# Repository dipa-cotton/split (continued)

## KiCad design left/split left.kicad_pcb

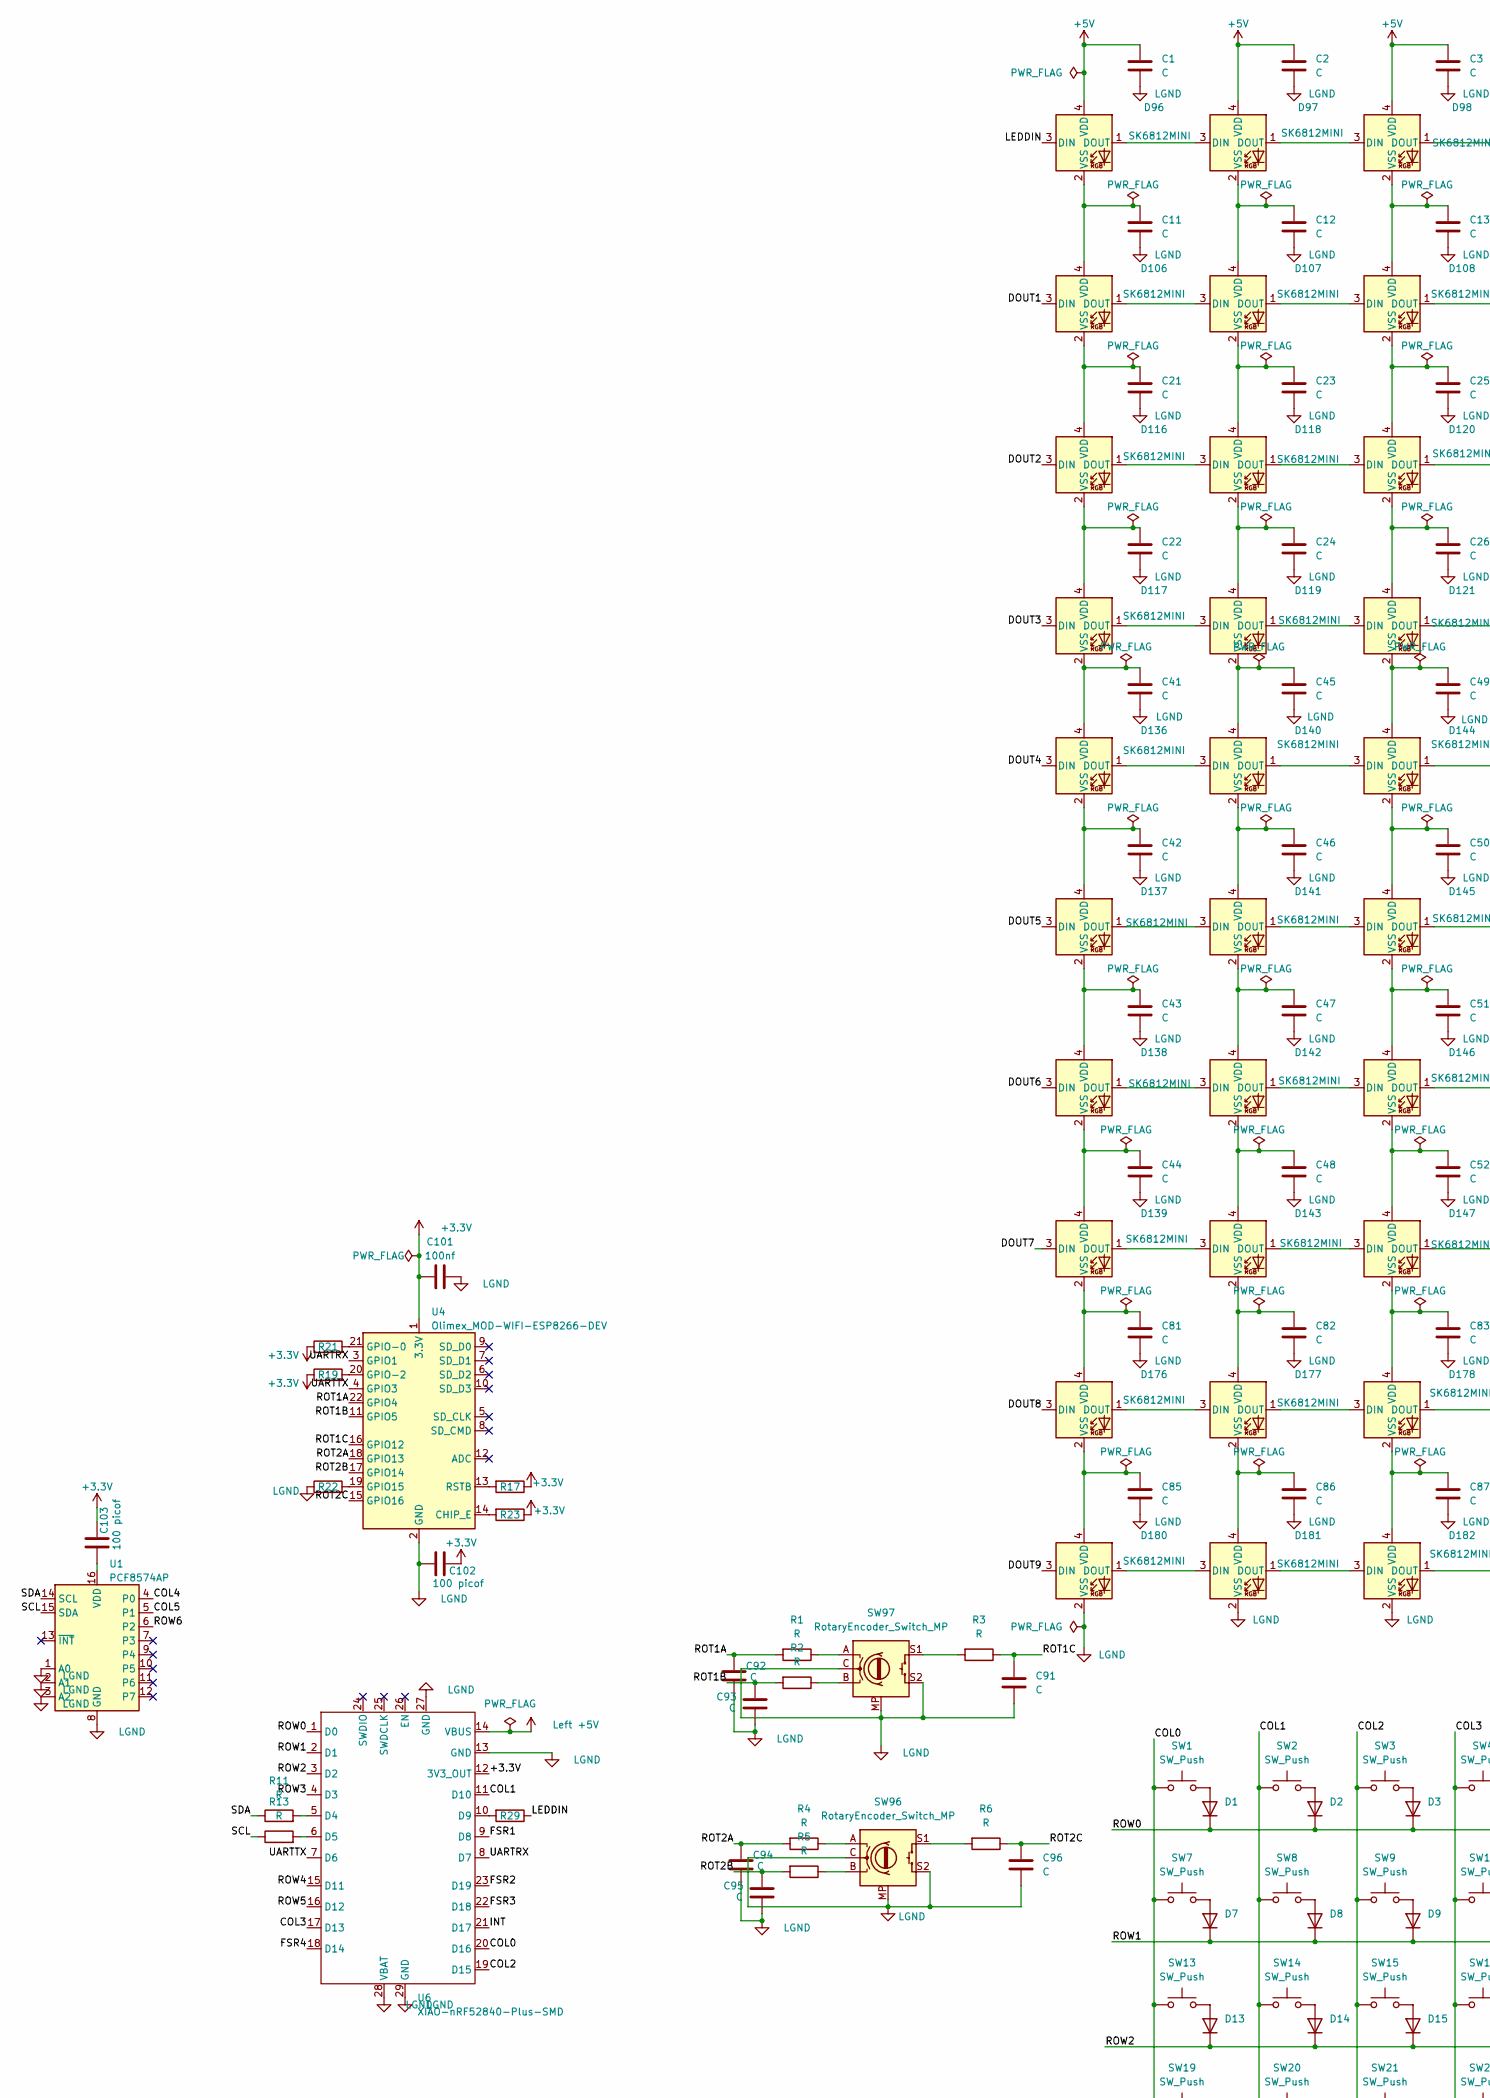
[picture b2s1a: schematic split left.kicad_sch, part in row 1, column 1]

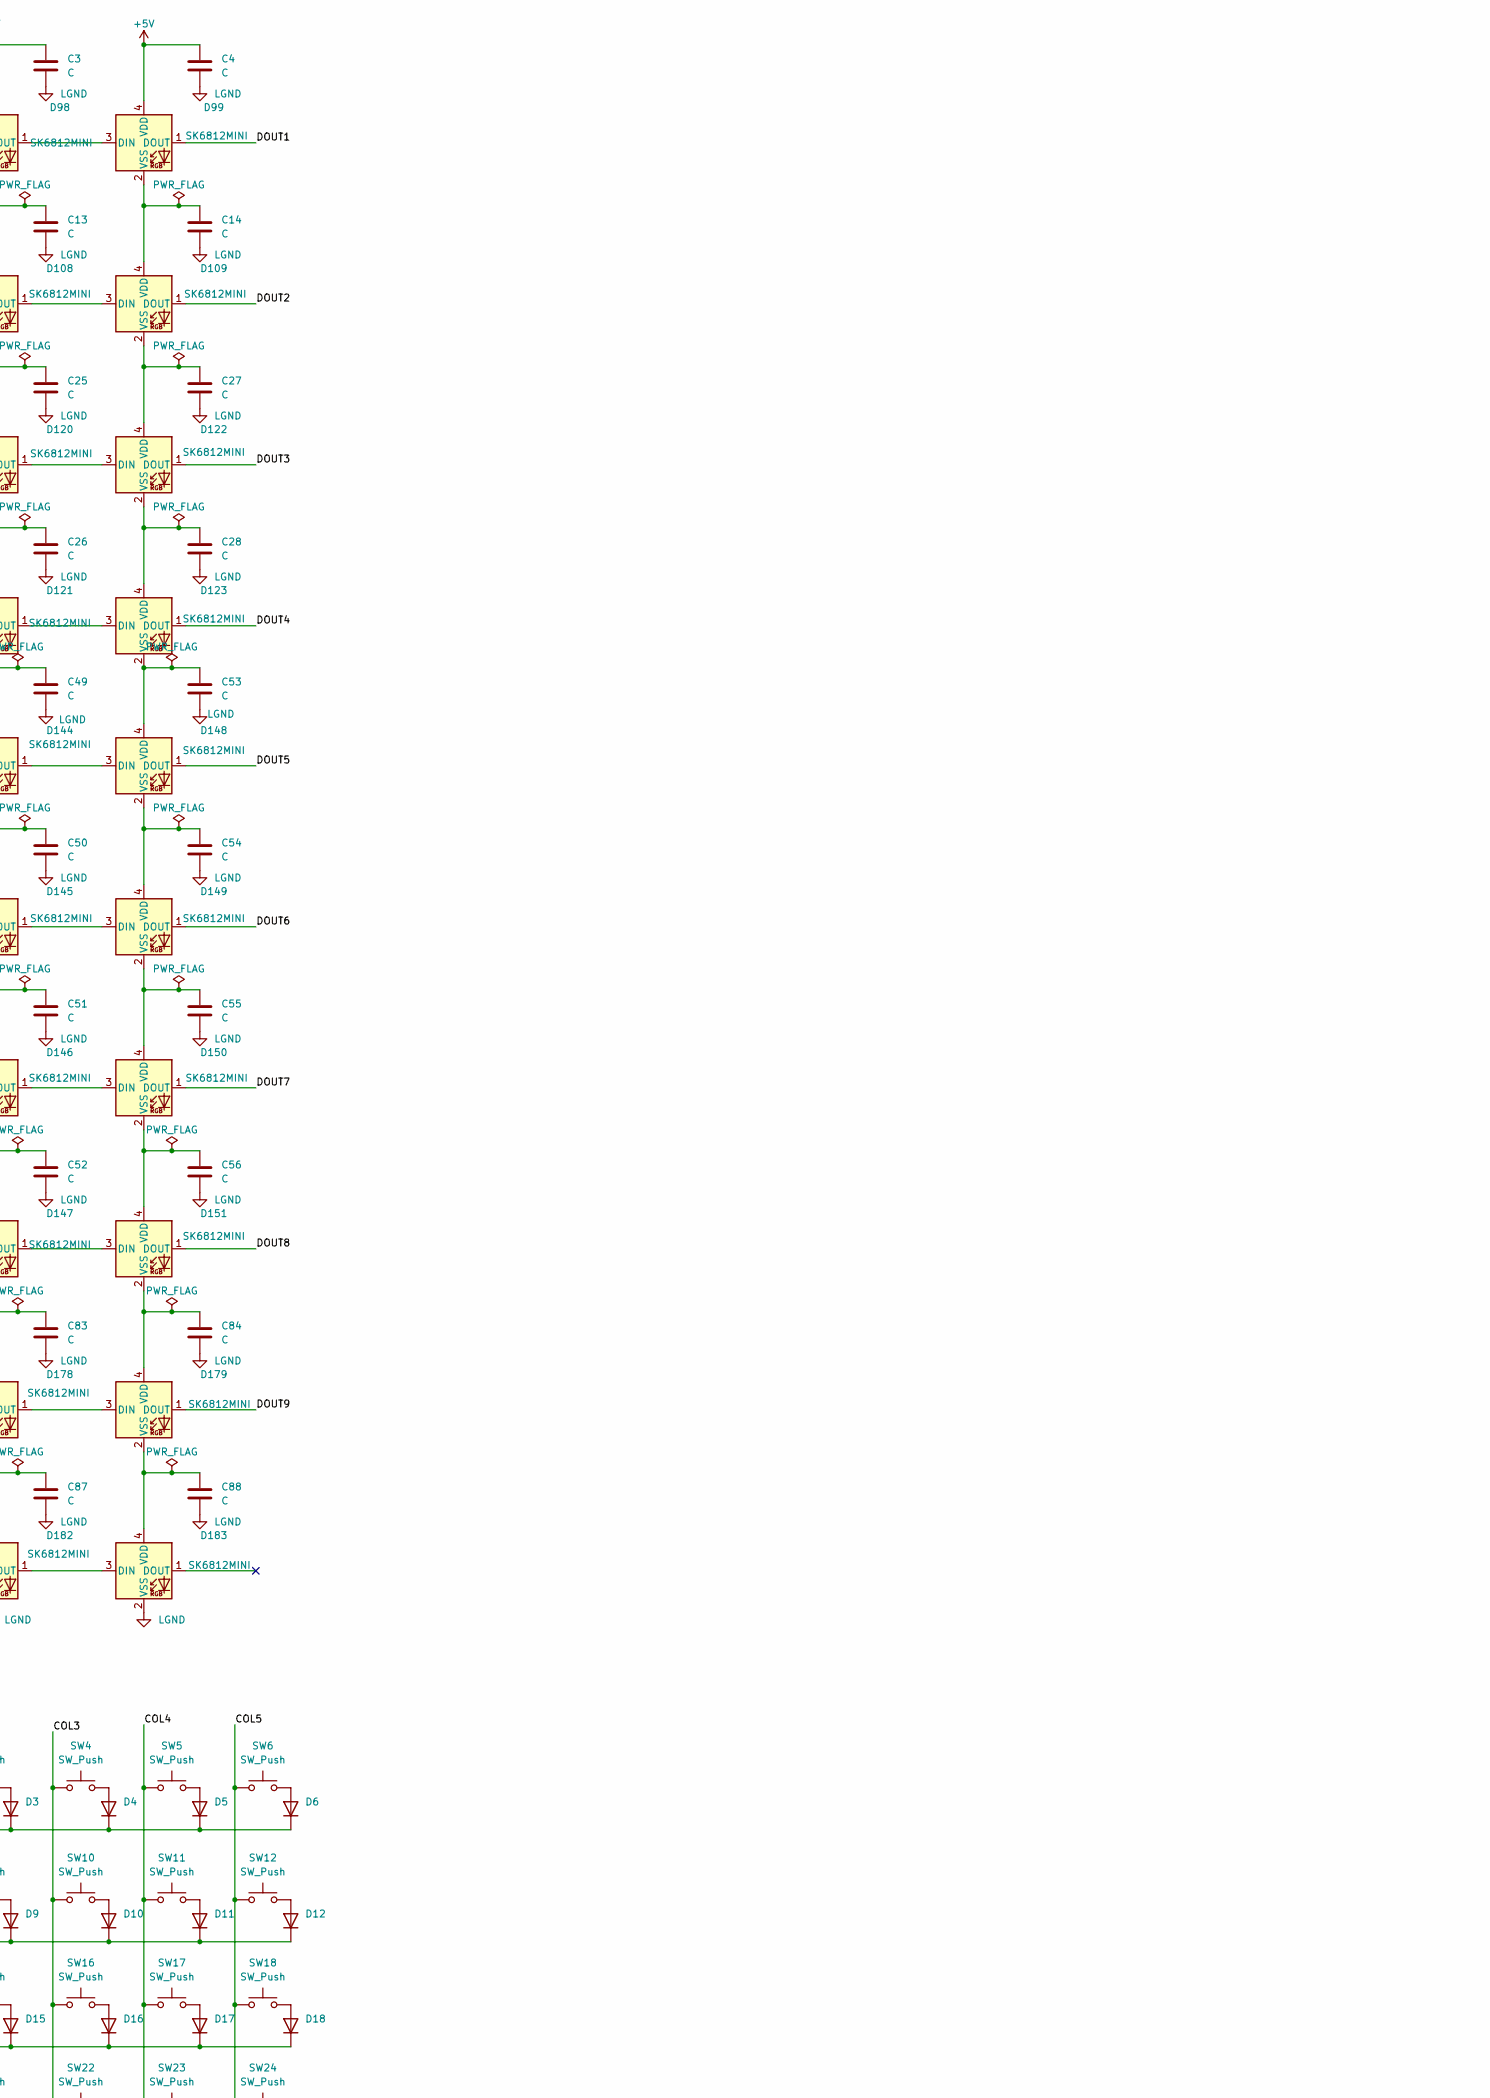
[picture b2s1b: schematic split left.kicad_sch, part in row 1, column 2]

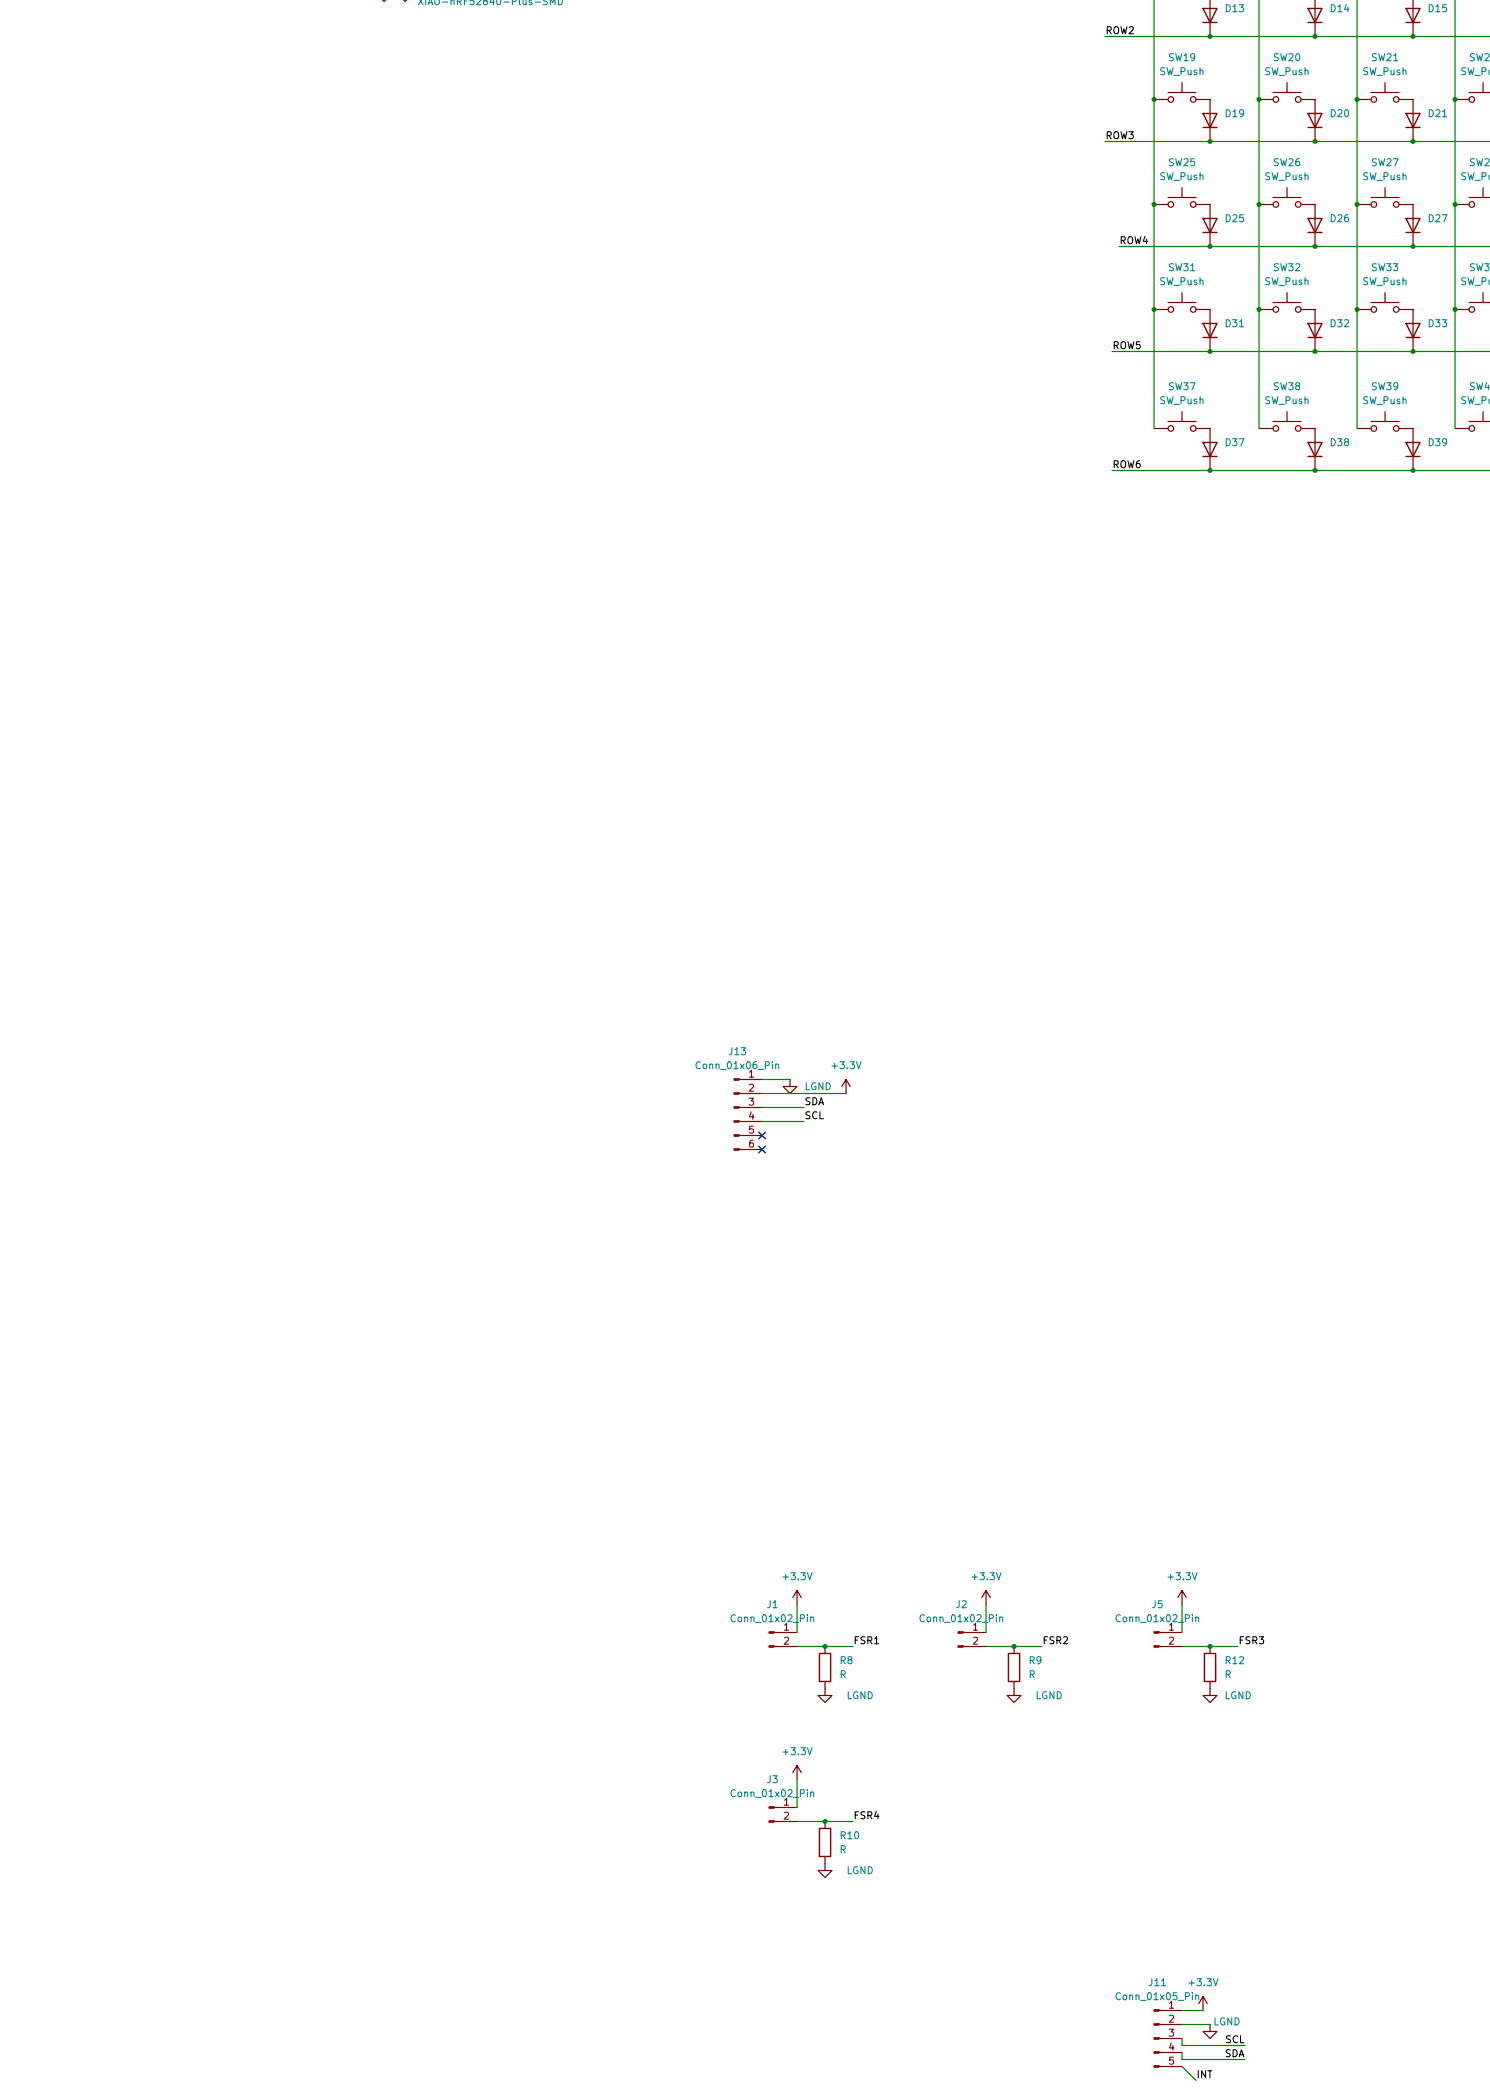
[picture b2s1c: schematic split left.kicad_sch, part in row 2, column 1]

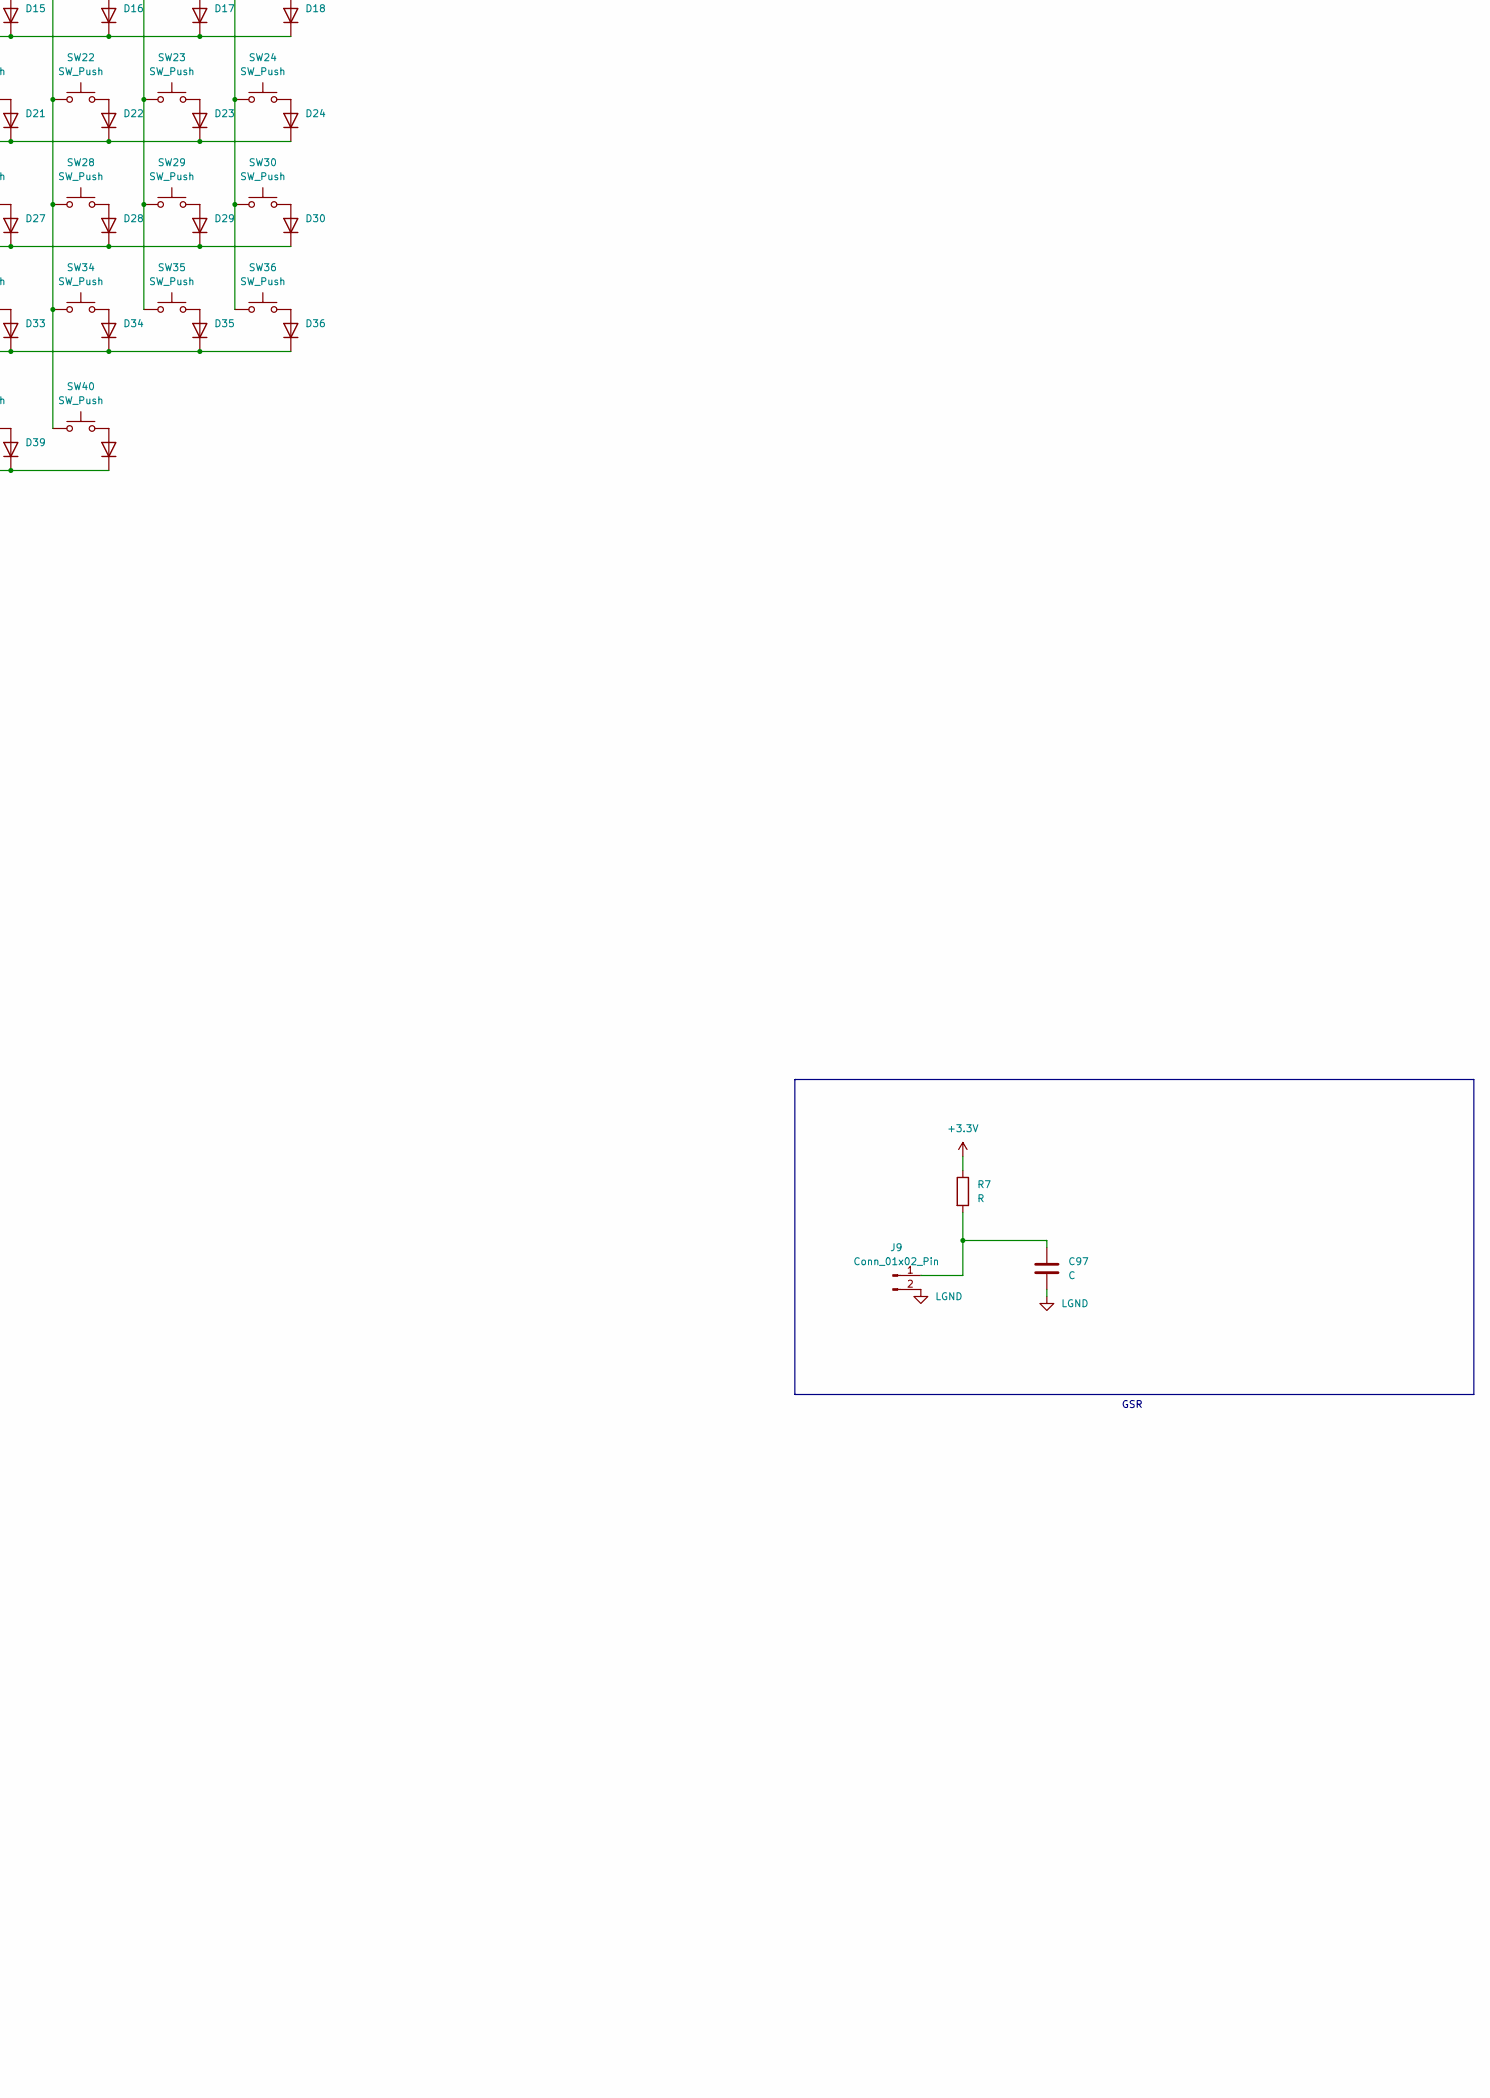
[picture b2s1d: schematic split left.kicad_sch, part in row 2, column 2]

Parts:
C1, C2, C3, C4, C11, C12, C13, C14, C21, C22, C23, C24, C25, C26, C27, C28, C41, C42, C43, C44, C45, C46, C47, C48, C49, C50, C51, C52, C53, C54, C55, C56, C81, C82, C83, C84, C85, C86, C87, C88, C91, C92, C93, C94, C95, C96, C97: C; C_0603_1608Metric
C101: 100nf; C_0603_1608Metric
C102, C103: 100 picof; C_0603_1608Metric
D1, D2, D3, D4, D5, D6, D7, D8, D9, D10, D11, D12, D13, D14, D15, D16, D17, D18, D19, D20, D21, D22, D23, D24, D25, D26, D27, D28, D29, D30, D31, D32, D33, D34, D35, D36, D37, D38, D39, D40: 1N914; C_0603_1608Metric
D96, D97, D98, D99, D106, D107, D108, D109, D116, D117, D118, D119, D120, D121, D122, D123, D136, D137, D138, D139, D140, D141, D142, D143, D144, D145, D146, D147, D148, D149, D150, D151, D176, D177, D178, D179, D180, D181, D182, D183: SK6812MINI; LED_SK6812MINI_PLCC4_3.5x3.5mm_P1.75mm
J1, J2, J3, J5, J9: Conn_01x02_Pin; TestPoint_Bridge_Pitch2.54mm_Drill1.0mm
J11: Conn_01x05_Pin; PinSocket_1x05_P2.54mm_Vertical
J13: Conn_01x06_Pin; PinHeader_1x06_P2.54mm_Vertical
R1, R2, R3, R4, R5, R6, R7, R8, R9, R10, R12, R17, R19, R21, R22, R23, R29: R; C_0603_1608Metric
R11, R13: R
SW1, SW2, SW3, SW4, SW5, SW6, SW7, SW8, SW9, SW10, SW11, SW12, SW13, SW14, SW15, SW16, SW17, SW18, SW19, SW20, SW21, SW22, SW23, SW24, SW25, SW26, SW27, SW28, SW29, SW30, SW31, SW32, SW33, SW34, SW35, SW36, SW37, SW38, SW39, SW40: SW_Push; SW_Cherry_MX_1.00u_PCB
SW96, SW97: RotaryEncoder_Switch_MP; RotaryEncoder_Alps_EC11E-Switch_Vertical_H20mm
U1: PCF8574AP; DIP-16_W7.62mm
U4: Olimex_MOD-WIFI-ESP8266-DEV
U6: XIAO-nRF52840-Plus-SMD

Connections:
+3.3V: C101.2, C102.1, C103.1, J1.1 (Pin_1_1), J2.1 (Pin_1_1), J3.1 (Pin_1_1), J5.1 (Pin_1_1), J11.1, J13.2, R7.1, R17.1, R19.1, R21.1, R23.1, U4.1 (3.3V), U6.12 (3V3_OUT)
+5V: C1.1, C2.1, C3.1, C4.1, D96.4 (VDD), D97.4 (VDD), D98.4 (VDD), D99.4 (VDD)
/COL0: SW1.1, SW7.1, SW13.1, SW19.1, SW25.1, SW31.1, SW37.1, U6.20 (D16)
/COL1: SW2.1, SW8.1, SW14.1, SW20.1, SW26.1, SW32.1, SW38.1, U6.11 (D10)
/COL2: SW3.1, SW9.1, SW15.1, SW21.1, SW27.1, SW33.1, SW39.1, U6.19 (D15)
/COL3: SW4.1, SW10.1, SW16.1, SW22.1, SW28.1, SW34.1, SW40.1, U6.17 (D13)
/COL4: SW5.1, SW11.1, SW17.1, SW23.1, SW29.1, SW35.1, U1.4 (P0)
/COL5: SW6.1, SW12.1, SW18.1, SW24.1, SW30.1, SW36.1, U1.5 (P1)
/DOUT1: D99.1 (DOUT), D106.3 (DIN)
/DOUT2: D109.1 (DOUT), D116.3 (DIN)
/DOUT3: D117.3 (DIN), D122.1 (DOUT)
/DOUT4: D123.1 (DOUT), D136.3 (DIN)
/DOUT5: D137.3 (DIN), D148.1 (DOUT)
/DOUT6: D138.3 (DIN), D149.1 (DOUT)
/DOUT7: D139.3 (DIN), D150.1 (DOUT)
/DOUT8: D151.1 (DOUT), D176.3 (DIN)
/DOUT9: D179.1 (DOUT), D180.3 (DIN)
/FSR1: J1.2, R8.1, U6.9 (D8)
/FSR2: J2.2, R9.1, U6.23 (D19)
/FSR3: J5.2, R12.1, U6.22 (D18)
/FSR4: J3.2, R10.1, U6.18 (D14)
/INT: J11.5, U6.21 (D17)
/LEDDIN: D96.3 (DIN), R29.1
/ROT1A: C92.1, R1.2, U4.22 (GPIO4)
/ROT1B: C93.1, R2.2, U4.11 (GPIO5)
/ROT1C: C91.1, R3.1, U4.16 (GPIO12)
/ROT2A: C94.1, R4.2, U4.18 (GPIO13)
/ROT2B: C95.1, R5.2, U4.17 (GPIO14)
/ROT2C: C96.1, R6.1, U4.15 (GPIO16)
/ROW0: D1.1 (K), D2.1 (K), D3.1 (K), D4.1 (K), D5.1 (K), D6.1 (K), U6.1 (D0)
/ROW1: D7.1 (K), D8.1 (K), D9.1 (K), D10.1 (K), D11.1 (K), D12.1 (K), U6.2 (D1)
/ROW2: D13.1 (K), D14.1 (K), D15.1 (K), D16.1 (K), D17.1 (K), D18.1 (K), U6.3 (D2)
/ROW3: D19.1 (K), D20.1 (K), D21.1 (K), D22.1 (K), D23.1 (K), D24.1 (K), U6.4 (D3)
/ROW4: D25.1 (K), D26.1 (K), D27.1 (K), D28.1 (K), D29.1 (K), D30.1 (K), U6.15 (D11)
/ROW5: D31.1 (K), D32.1 (K), D33.1 (K), D34.1 (K), D35.1 (K), D36.1 (K), U6.16 (D12)
/ROW6: D37.1 (K), D38.1 (K), D39.1 (K), D40.1 (K), U1.6 (P2)
/SCL: J11.3, J13.4, R13.1, U1.15 (SDA)
/SDA: J11.4, J13.3, R11.1, U1.14 (SCL)
/UARTRX: U4.3 (GPIO1), U6.8 (D7)
/UARTTX: U4.4 (GPIO3), U6.7 (D6)
LGND: C1.2, C2.2, C3.2, C4.2, C11.2, C12.2, C13.2, C14.2, C21.2, C22.2, C23.2, C24.2, C25.2, C26.2, C27.2, C28.2, C41.2, C42.2, C43.2, C44.2, C45.2, C46.2, C47.2, C48.2, C49.2, C50.2, C51.2, C52.2, C53.2, C54.2, C55.2, C56.2, C81.2, C82.2, C83.2, C84.2, C85.2, C86.2, C87.2, C88.2, C91.2, C92.2, C93.2, C94.2, C95.2, C96.2, C97.2, C101.1, C102.2, D180.2 (VSS), D181.2 (VSS), D182.2 (VSS), D183.2 (VSS), J9.2, J11.2, J13.1, R8.2, R9.2, R10.2, R12.2, R22.1, SW96.C, SW96.MP, SW96.S2, SW97.C, SW97.MP, SW97.S2, U1.1 (A0), U1.2 (A1), U1.3 (A2), U1.8 (GND), U4.2 (GND), U6.13 (GND), U6.27 (GND), U6.28 (VBAT), U6.29 (GND)
Left +5V: U6.14 (VBUS)
unnamed: D1.2 (A), SW1.2
unnamed: D2.2 (A), SW2.2
unnamed: D3.2 (A), SW3.2
unnamed: D4.2 (A), SW4.2
unnamed: D5.2 (A), SW5.2
unnamed: D6.2 (A), SW6.2
unnamed: D7.2 (A), SW7.2
unnamed: D8.2 (A), SW8.2
unnamed: D9.2 (A), SW9.2
unnamed: D10.2 (A), SW10.2
unnamed: D11.2 (A), SW11.2
unnamed: D12.2 (A), SW12.2
unnamed: D13.2 (A), SW13.2
unnamed: D14.2 (A), SW14.2
unnamed: D15.2 (A), SW15.2
unnamed: D16.2 (A), SW16.2
unnamed: D17.2 (A), SW17.2
unnamed: D18.2 (A), SW18.2
unnamed: D19.2 (A), SW19.2
unnamed: D20.2 (A), SW20.2
unnamed: D21.2 (A), SW21.2
unnamed: D22.2 (A), SW22.2
unnamed: D23.2 (A), SW23.2
unnamed: D24.2 (A), SW24.2
unnamed: D25.2 (A), SW25.2
unnamed: D26.2 (A), SW26.2
unnamed: D27.2 (A), SW27.2
unnamed: D28.2 (A), SW28.2
unnamed: D29.2 (A), SW29.2
unnamed: D30.2 (A), SW30.2
unnamed: D31.2 (A), SW31.2
unnamed: D32.2 (A), SW32.2
unnamed: D33.2 (A), SW33.2
unnamed: D34.2 (A), SW34.2
unnamed: D35.2 (A), SW35.2
unnamed: D36.2 (A), SW36.2
unnamed: D37.2 (A), SW37.2
unnamed: D38.2 (A), SW38.2
unnamed: D39.2 (A), SW39.2
unnamed: D40.2 (A), SW40.2
unnamed: D96.1 (DOUT), D97.3 (DIN)
unnamed: D97.1 (DOUT), D98.3 (DIN)
unnamed: D98.1 (DOUT), D99.3 (DIN)
unnamed: D106.1 (DOUT), D107.3 (DIN)
unnamed: C11.1, D96.2 (VSS), D106.4 (VDD)
unnamed: C21.1, D106.2 (VSS), D116.4 (VDD)
unnamed: D107.1 (DOUT), D108.3 (DIN)
unnamed: C12.1, D97.2 (VSS), D107.4 (VDD)
unnamed: C23.1, D107.2 (VSS), D118.4 (VDD)
unnamed: D108.1 (DOUT), D109.3 (DIN)
unnamed: C13.1, D98.2 (VSS), D108.4 (VDD)
unnamed: C25.1, D108.2 (VSS), D120.4 (VDD)
unnamed: C14.1, D99.2 (VSS), D109.4 (VDD)
unnamed: C27.1, D109.2 (VSS), D122.4 (VDD)
unnamed: D116.1 (DOUT), D118.3 (DIN)
unnamed: C22.1, D116.2 (VSS), D117.4 (VDD)
unnamed: D117.1 (DOUT), D119.3 (DIN)
unnamed: C41.1, D117.2 (VSS), D136.4 (VDD)
unnamed: D118.1 (DOUT), D120.3 (DIN)
unnamed: C24.1, D118.2 (VSS), D119.4 (VDD)
unnamed: D119.1 (DOUT), D121.3 (DIN)
unnamed: C45.1, D119.2 (VSS), D140.4 (VDD)
unnamed: D120.1 (DOUT), D122.3 (DIN)
unnamed: C26.1, D120.2 (VSS), D121.4 (VDD)
unnamed: D121.1 (DOUT), D123.3 (DIN)
unnamed: C49.1, D121.2 (VSS), D144.4 (VDD)
unnamed: C28.1, D122.2 (VSS), D123.4 (VDD)
unnamed: C53.1, D123.2 (VSS), D148.4 (VDD)
unnamed: D136.1 (DOUT), D140.3 (DIN)
unnamed: C42.1, D136.2 (VSS), D137.4 (VDD)
unnamed: D137.1 (DOUT), D141.3 (DIN)
unnamed: C43.1, D137.2 (VSS), D138.4 (VDD)
unnamed: D138.1 (DOUT), D142.3 (DIN)
unnamed: C44.1, D138.2 (VSS), D139.4 (VDD)
unnamed: D139.1 (DOUT), D143.3 (DIN)
unnamed: C81.1, D139.2 (VSS), D176.4 (VDD)
unnamed: D140.1 (DOUT), D144.3 (DIN)
unnamed: C46.1, D140.2 (VSS), D141.4 (VDD)
unnamed: D141.1 (DOUT), D145.3 (DIN)
unnamed: C47.1, D141.2 (VSS), D142.4 (VDD)
unnamed: D142.1 (DOUT), D146.3 (DIN)
unnamed: C48.1, D142.2 (VSS), D143.4 (VDD)
unnamed: D143.1 (DOUT), D147.3 (DIN)
unnamed: C82.1, D143.2 (VSS), D177.4 (VDD)
unnamed: D144.1 (DOUT), D148.3 (DIN)
unnamed: C50.1, D144.2 (VSS), D145.4 (VDD)
unnamed: D145.1 (DOUT), D149.3 (DIN)
unnamed: C51.1, D145.2 (VSS), D146.4 (VDD)
unnamed: D146.1 (DOUT), D150.3 (DIN)
unnamed: C52.1, D146.2 (VSS), D147.4 (VDD)
unnamed: D147.1 (DOUT), D151.3 (DIN)
unnamed: C83.1, D147.2 (VSS), D178.4 (VDD)
unnamed: C54.1, D148.2 (VSS), D149.4 (VDD)
unnamed: C55.1, D149.2 (VSS), D150.4 (VDD)
unnamed: C56.1, D150.2 (VSS), D151.4 (VDD)
unnamed: C84.1, D151.2 (VSS), D179.4 (VDD)
unnamed: D176.1 (DOUT), D177.3 (DIN)
unnamed: C85.1, D176.2 (VSS), D180.4 (VDD)
unnamed: D177.1 (DOUT), D178.3 (DIN)
unnamed: C86.1, D177.2 (VSS), D181.4 (VDD)
unnamed: D178.1 (DOUT), D179.3 (DIN)
unnamed: C87.1, D178.2 (VSS), D182.4 (VDD)
unnamed: C88.1, D179.2 (VSS), D183.4 (VDD)
unnamed: D180.1 (DOUT), D181.3 (DIN)
unnamed: D181.1 (DOUT), D182.3 (DIN)
unnamed: D182.1 (DOUT), D183.3 (DIN)
unnamed: C97.1, J9.1 (Pin_1_1), R7.2
unnamed: R1.1, SW97.A
unnamed: R2.1, SW97.B
unnamed: R3.2, SW97.S1
unnamed: R4.1, SW96.A
unnamed: R5.1, SW96.B
unnamed: R6.2, SW96.S1
unnamed: C103.2, U1.16 (VDD)
unnamed: R23.2, U4.14 (CHIP_E)
unnamed: R22.2, U4.19 (GPIO15)
unnamed: R21.2, U4.21 (GPIO-0)
unnamed: R19.2, U4.20 (GPIO-2)
unnamed: R17.2, U4.13 (RSTB)
unnamed: R11.2, U6.5 (D4)
unnamed: R13.2, U6.6 (D5)
unnamed: R29.2, U6.10 (D9)

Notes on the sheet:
GSR

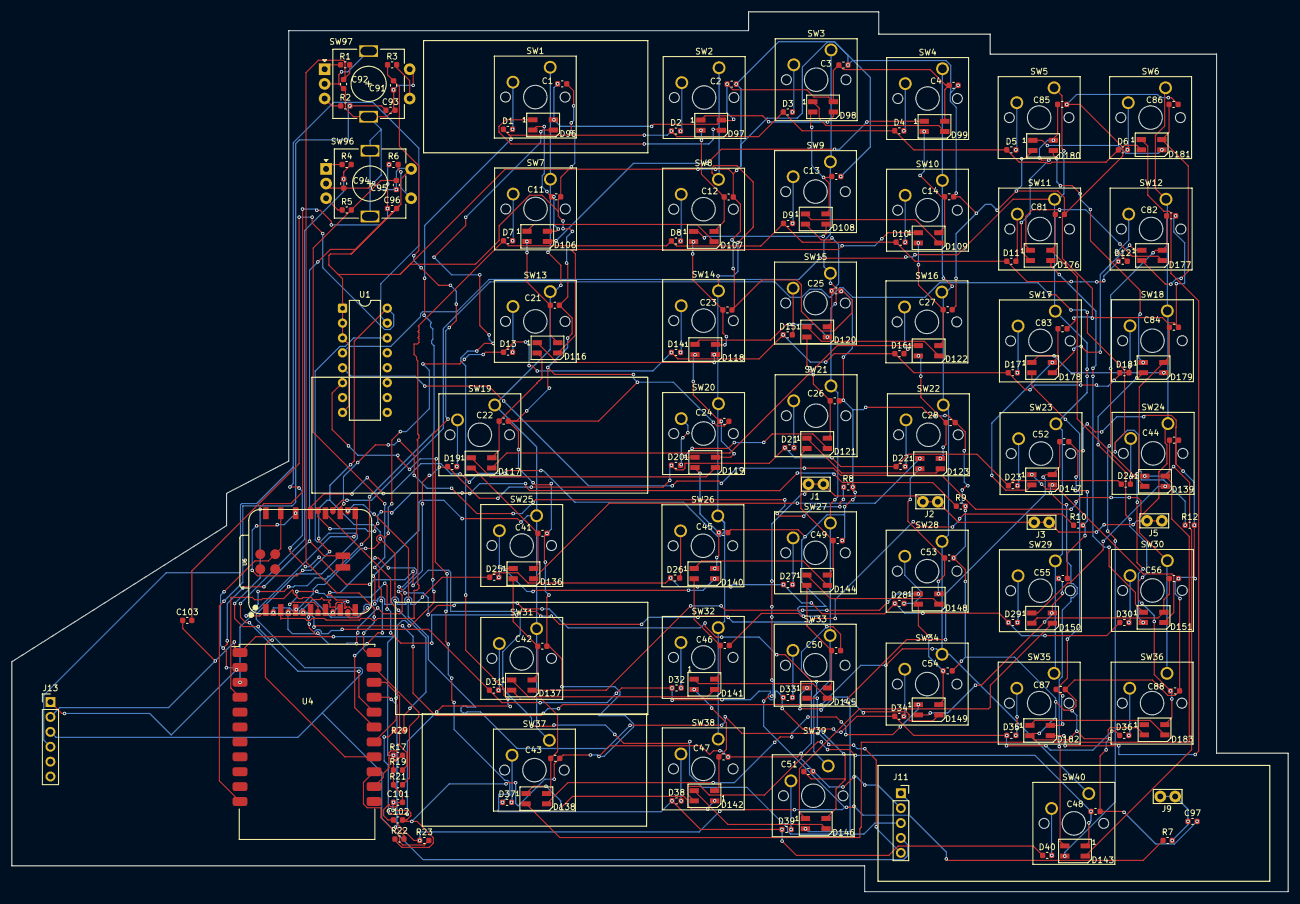
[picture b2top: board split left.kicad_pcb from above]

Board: 2 copper layers, 217.6 x 150.0 mm, 199 parts (0 on the bottom side), 161 nets.
